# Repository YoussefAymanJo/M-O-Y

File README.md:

# M-O-Y

## Description 

M-O-Y is an abbreviation for Microbe-Obliterator For Youssef.in other words its is Virtual colleague compannion on my desk customized for me.Can answer i ask him abut weather , latest news, movies.it not just ai agent,but it interactive colleague react with mu during dancing or working lockin.I powered by esp32 S3
It is originated from the M-O cleaning robot form Wall-E movie,with his funny character and decipline to clean.It has vioce and make can hear me.

## Why it was built

Actually,i feel boring and uncomfortable on my studying and working hours on my study or on pc.so,i made this robot to be ai companion for me. Interact with my emotiions and answer my questions.Moreover,i was such a big fan of wall -e movie specially M-O ,so i decided to make this project.

## How to use it / Build it
Firstly,buy circuit componets and fabricate PCB.After that sold componets on PCB and wire circuit part togehter,then wire batteries with BMS module and charger.
After that upload code and test it on circuit ,editing also.
Finally,fabricat 3d printed enlcouuree and assebmle them with circuit using glue and scews.

## Schemtatic
I made a schematic for my Robot, and sketch simpled diagram for the schematic.

## PCB
I outlined shape first, then routed the PCB and added 3d models

## CAD 

## Firmware 

## BOM

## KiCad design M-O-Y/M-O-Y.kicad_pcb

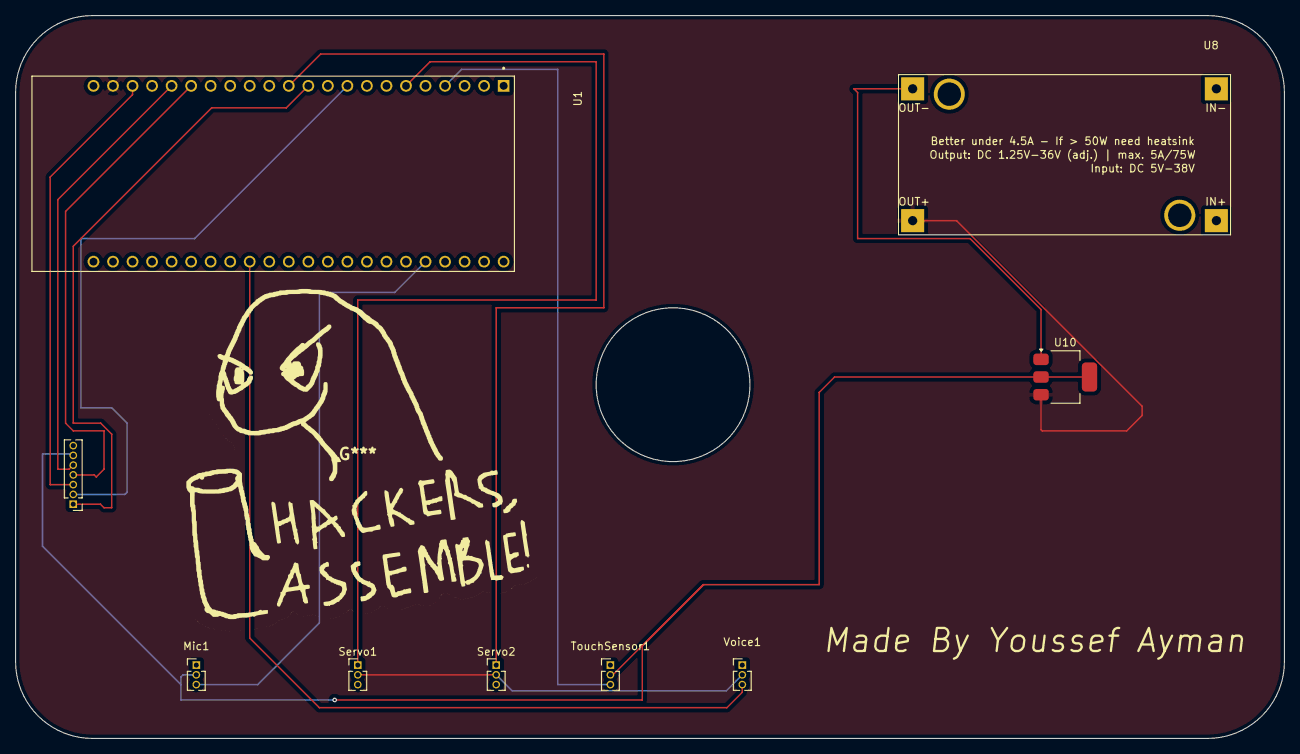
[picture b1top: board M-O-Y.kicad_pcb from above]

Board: 2 copper layers, 165.0 x 94.0 mm, 9 parts (0 on the bottom side), 13 nets.

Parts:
Mic1: Conn_01x03_Pin; PinHeader_1x03_P1.27mm_Vertical
Servo1, Servo2: Conn_01x03_Pin; PinHeader_1x03_P1.27mm_Vertical
TFT1.5inch1: Conn_01x07_Pin; PinHeader_1x07_P1.27mm_Vertical
TouchSensor1: Conn_01x03_Pin; PinHeader_1x03_P1.27mm_Vertical
U1: ESP32-S3-DEVKITC-1-N8R2; XCVR_ESP32-S3-DEVKITC-1-N8R2
U8: Step_Down +5v; XL4005_DC-DC
U10: AMS1117-3.3; SOT-223-3_TabPin2
Voice1: Conn_01x03_Pin; PinHeader_1x03_P1.27mm_Vertical

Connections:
3.3: Mic1.2, TFT1.5inch1.6, TouchSensor1.2, U10.2 (VO)
GND: Mic1.1, Servo1.3, Servo2.3, TFT1.5inch1.7, TouchSensor1.1, U1.J1_22 (GND), U1.J3_1 (GND), U1.J3_21 (GND), U1.J3_22 (GND), U8.4 (OUT-), U10.1 (GND), Voice1.1
Imax_I2c: U1.J3_14 (GPIO0), Voice1.3
M1: Servo1.1, U1.J1_6 (GPIO6)
M2: Servo2.1, U1.J1_12 (GPIO8)
Mic_I2c: Mic1.3, U1.J3_5 (GPIO2)
On/of: TouchSensor1.3, U1.J1_4 (GPIO4)
SCL: TFT1.5inch1.5, U1.J1_18 (GPIO12)
SDA: TFT1.5inch1.4, U1.J1_17 (GPIO11)
VCC: Servo1.2, Servo2.2, U1.J1_21 (5V0), U8.3 (OUT+), U10.3 (VI), Voice1.2
display1: TFT1.5inch1.3, U1.J1_20 (GPIO14)
display_2: TFT1.5inch1.2, U1.J1_9 (GPIO16)
display_3: TFT1.5inch1.1, U1.J1_11 (GPIO18)
